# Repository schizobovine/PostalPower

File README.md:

# PostalPower
Postage-stamp (US) sized PCBs for stupid &amp; simple shit like DC-DC linear converters or LED drivers.

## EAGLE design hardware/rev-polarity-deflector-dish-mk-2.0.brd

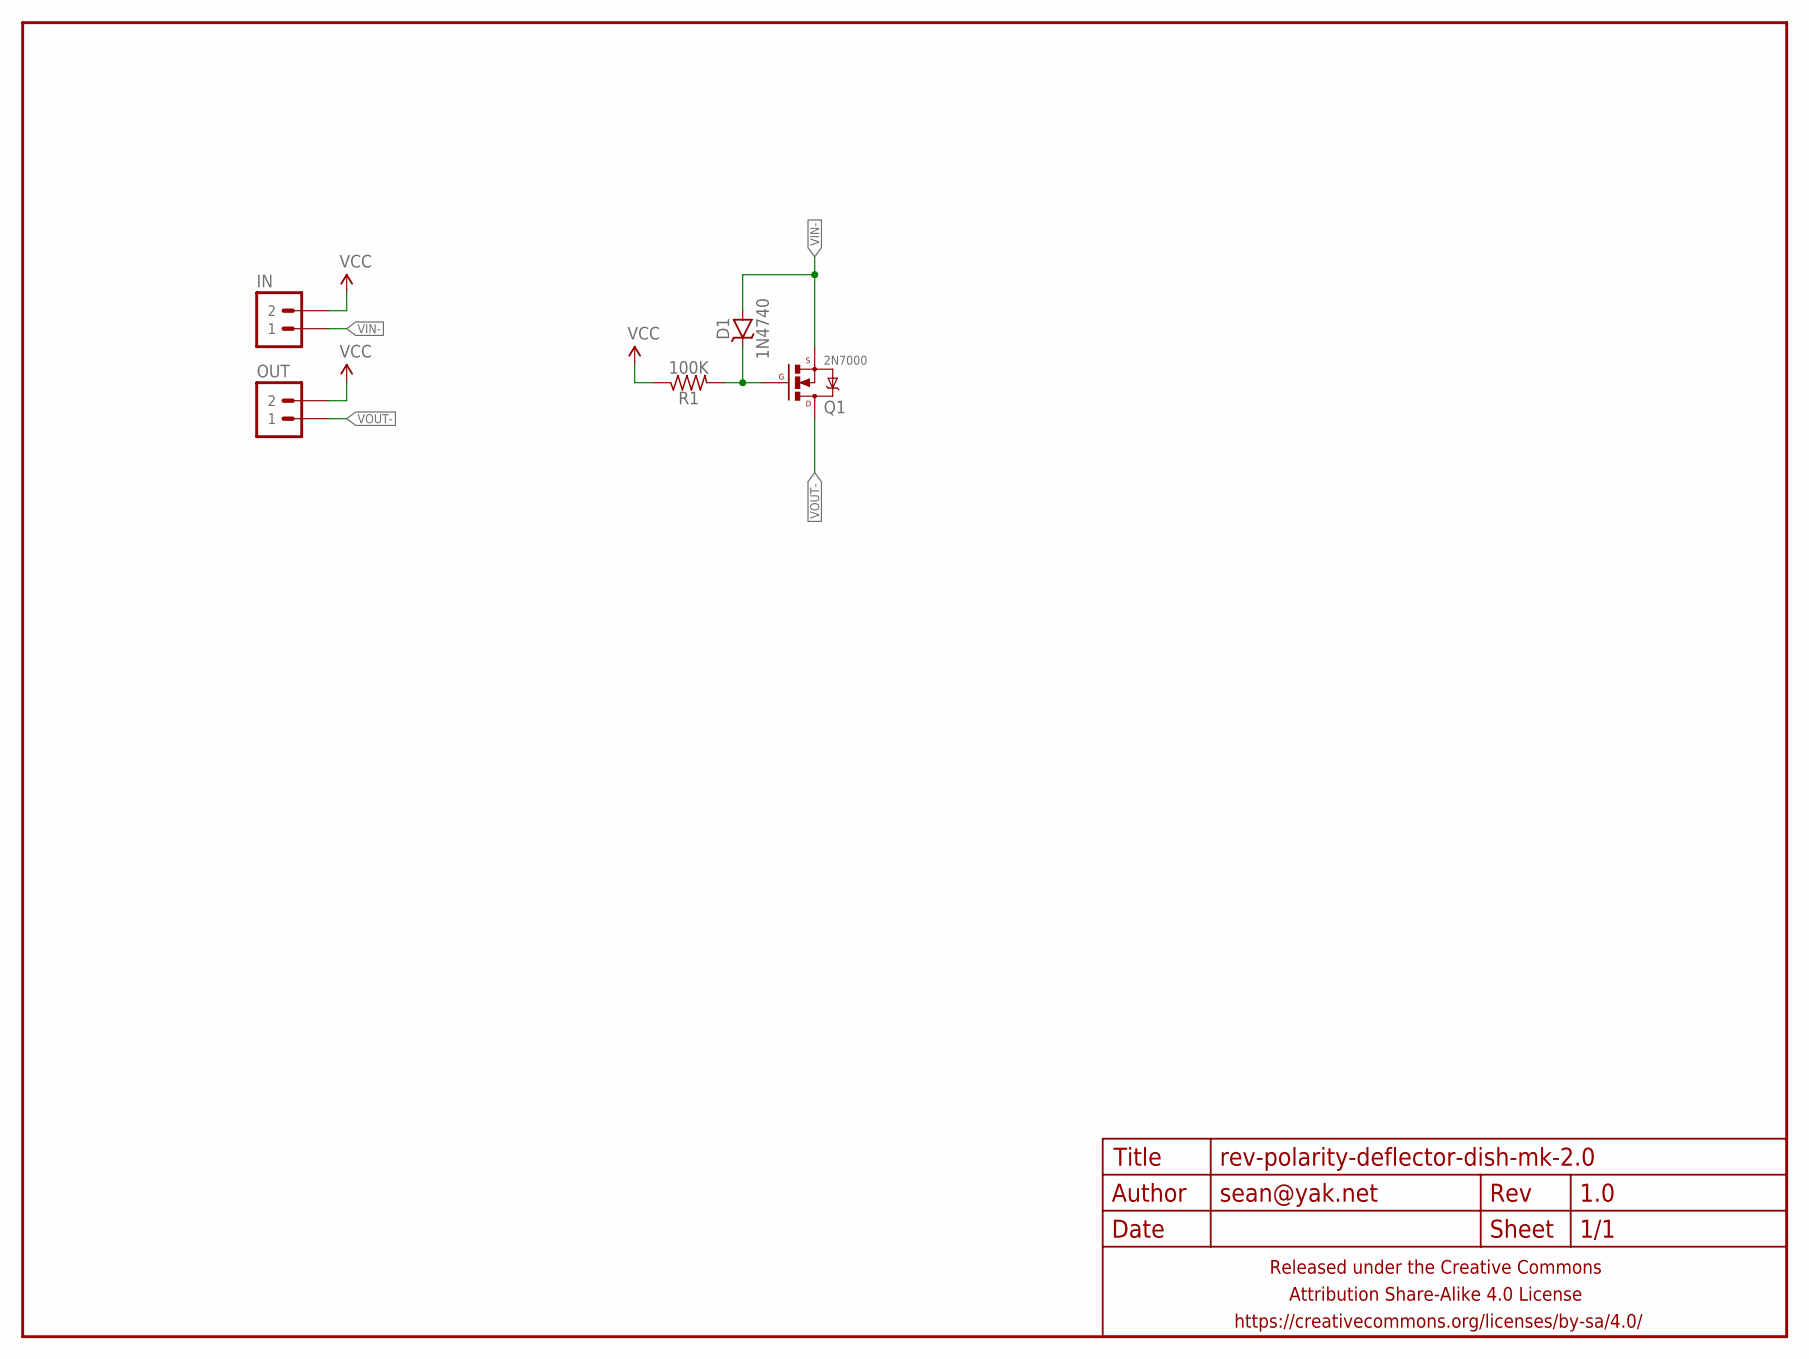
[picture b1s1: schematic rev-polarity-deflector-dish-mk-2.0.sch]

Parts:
D1: 1N4740; SOT23
FRAME1: FRAME-LETTERNO_PACKAGE; DUMMY
IN: M02PTH-CENTERED; 1X02-CENTER
OUT: M02PTH-CENTERED; 1X02-CENTER
Q1: 2N7000; SOT23
R1: 100K; R0603

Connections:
unnamed: D1.3 (C), Q1.1 (G), R1.2
VCC: IN.2, OUT.2, R1.1
VIN-: D1.1 (A), D1.2 (A), IN.1, Q1.2 (S)
VOUT-: OUT.1, Q1.3 (D)

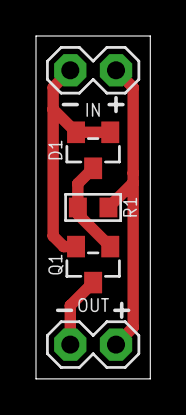
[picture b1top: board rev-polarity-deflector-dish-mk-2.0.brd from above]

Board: 2 copper layers, 6.3 x 19.1 mm, 6 parts (0 on the bottom side), 4 nets.

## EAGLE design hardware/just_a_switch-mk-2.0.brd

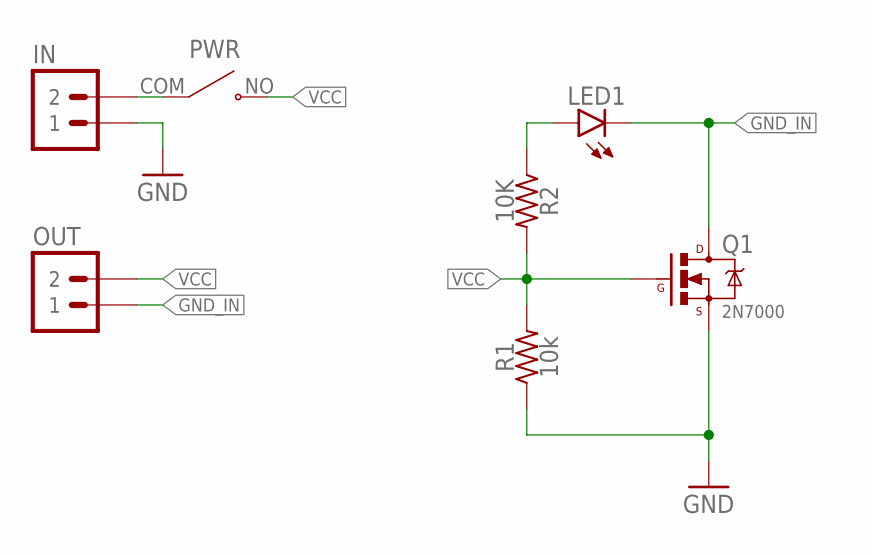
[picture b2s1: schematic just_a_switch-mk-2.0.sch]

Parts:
IN: M02PTH-CENTERED-R+; 1X02-CENTER-R+
LED1: LED3MM-LESS; LED3MM-LESSSILK
OUT: M02PTH-CENTERED-R+; 1X02-CENTER-R+
PWR: SWITCH-SPSTROCKER; SPST-ROCKER-3.81MM
Q1: 2N7000; TO-92-AMMO
R1: 10k; RESISTOR-AXIAL-PTH-5.08MM
R2: 10K; RESISTOR-AXIAL-PTH-5.08MM

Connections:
GND: IN.1, Q1.1 (S), R1.P$1 (1)
GND_IN: LED1.K (C), OUT.1, Q1.3 (D)
unnamed: IN.2, PWR.COM
unnamed: LED1.A, R2.P$1 (1)
VCC: OUT.2, PWR.NO, Q1.2 (G), R1.P$2 (2), R2.P$2 (2)

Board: 2 copper layers, 7 parts (2 on the bottom side), 5 nets, no tracks yet.

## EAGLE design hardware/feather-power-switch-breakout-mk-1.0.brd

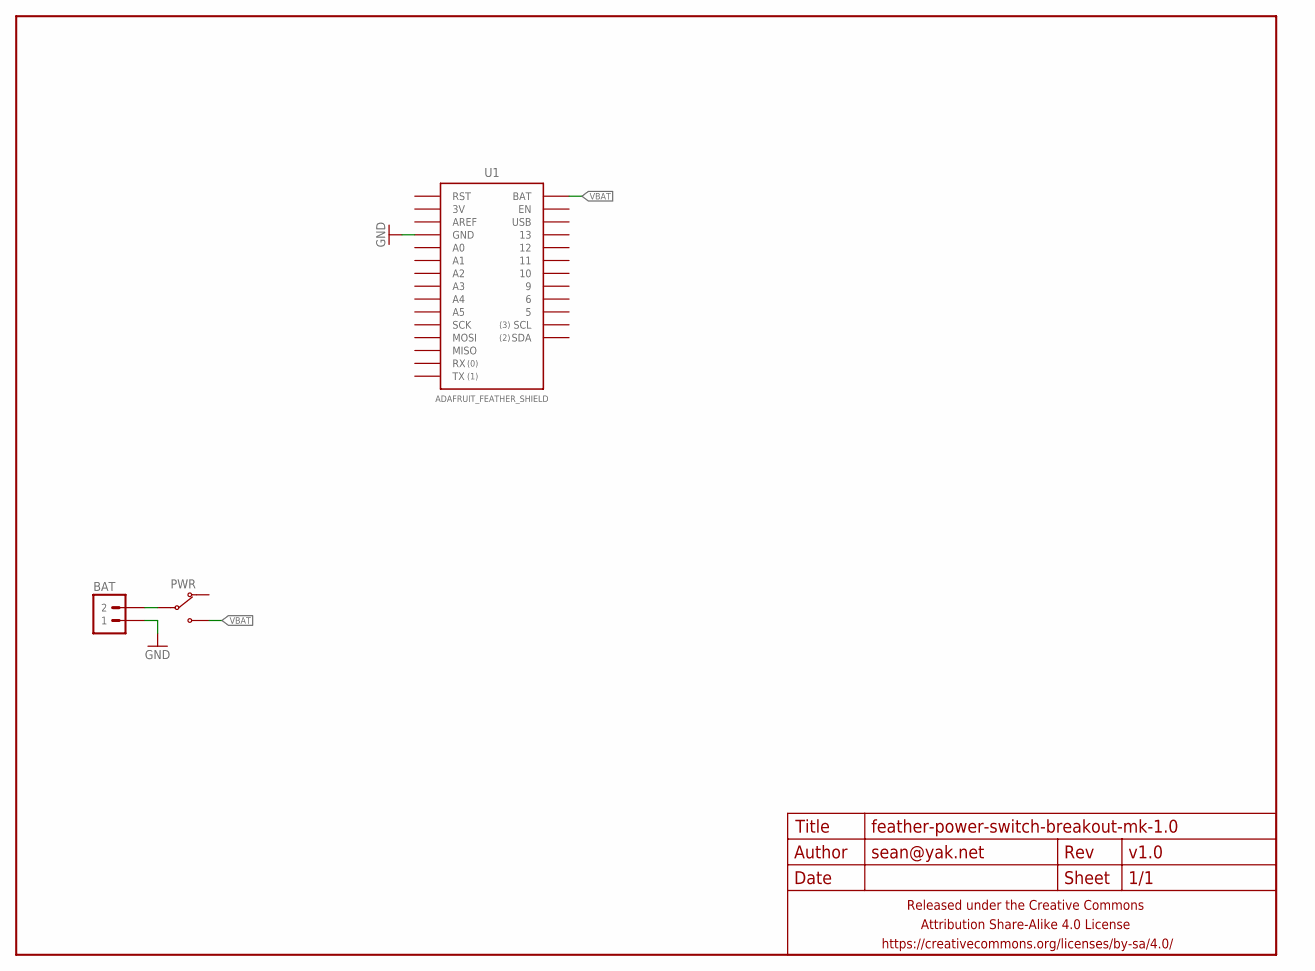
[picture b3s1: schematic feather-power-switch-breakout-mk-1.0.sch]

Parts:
BAT: M02JST-PTH-RA-R+; JST-2-PH-RA-PTH-R+
FRAME1: FRAME-LETTERNO_PACKAGE; DUMMY
PWR: SWITCH-SPDTPTH-RA-2.54MM; SPDT-RA-2.54MM
U1: ADAFRUIT_FEATHER_SHIELD; ADAFRUIT_FEATHER

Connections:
GND: BAT.1, U1.GND@0 (GND), U1.GND@1 (GND)
unnamed: BAT.2, PWR.2 (COM)
VBAT: PWR.3 (NO), U1.BAT

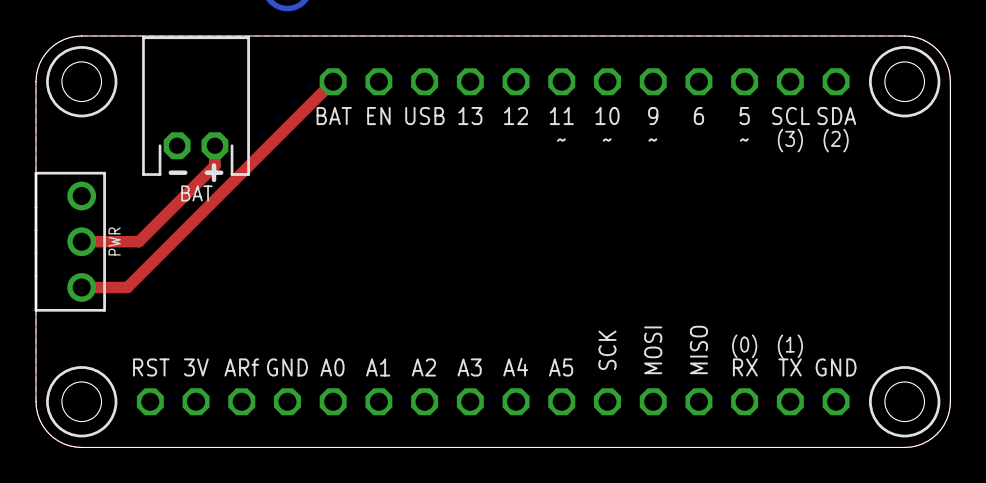
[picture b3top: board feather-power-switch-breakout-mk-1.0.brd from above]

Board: 2 copper layers, 50.8 x 22.9 mm, 5 parts (1 on the bottom side), 3 nets.

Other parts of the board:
U$1: COW_SMALL_METAL_NOTEXT

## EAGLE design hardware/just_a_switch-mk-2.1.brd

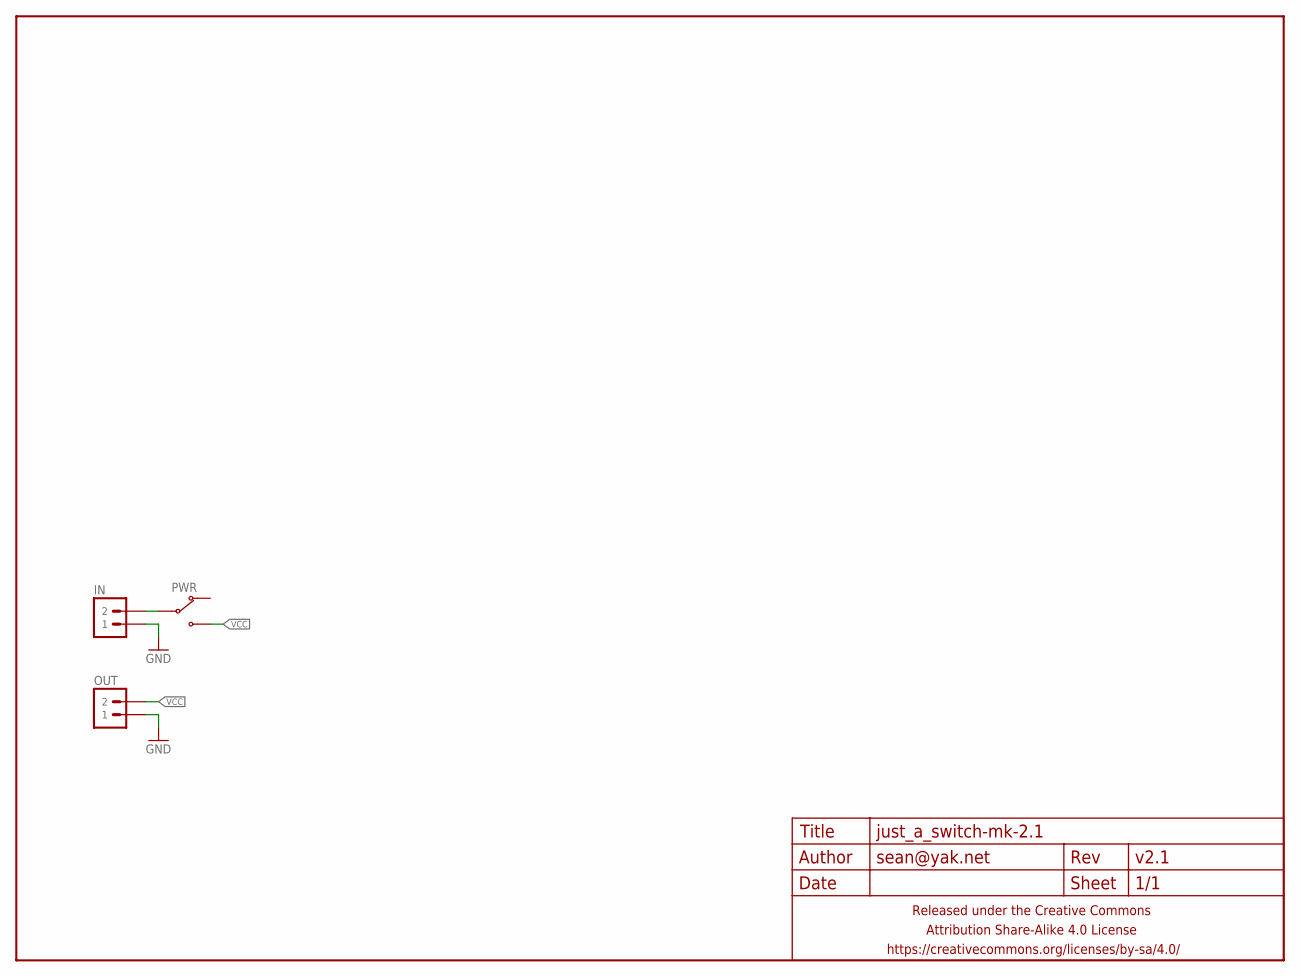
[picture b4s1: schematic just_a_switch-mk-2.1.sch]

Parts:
FRAME1: FRAME-LETTERNO_PACKAGE; DUMMY
IN: M02JST-PH-VERT-R+; JST-2-PH-VERT-PTH-R+
OUT: M02JST-PH-VERT-R+; JST-2-PH-VERT-PTH-R+
PWR: SWITCH-SPDTPTH-RA-2.54MM; SPDT-RA-2.54MM

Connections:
GND: IN.1, OUT.1
unnamed: IN.2, PWR.2 (COM)
VCC: OUT.2, PWR.3 (NO)

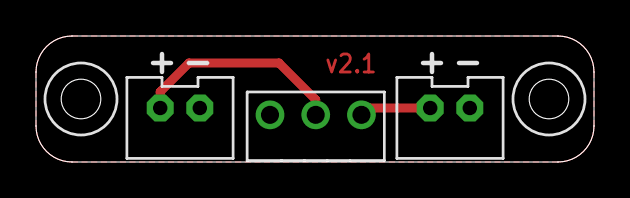
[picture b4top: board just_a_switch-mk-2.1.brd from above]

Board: 2 copper layers, 31.0 x 7.0 mm, 4 parts (0 on the bottom side), 3 nets.

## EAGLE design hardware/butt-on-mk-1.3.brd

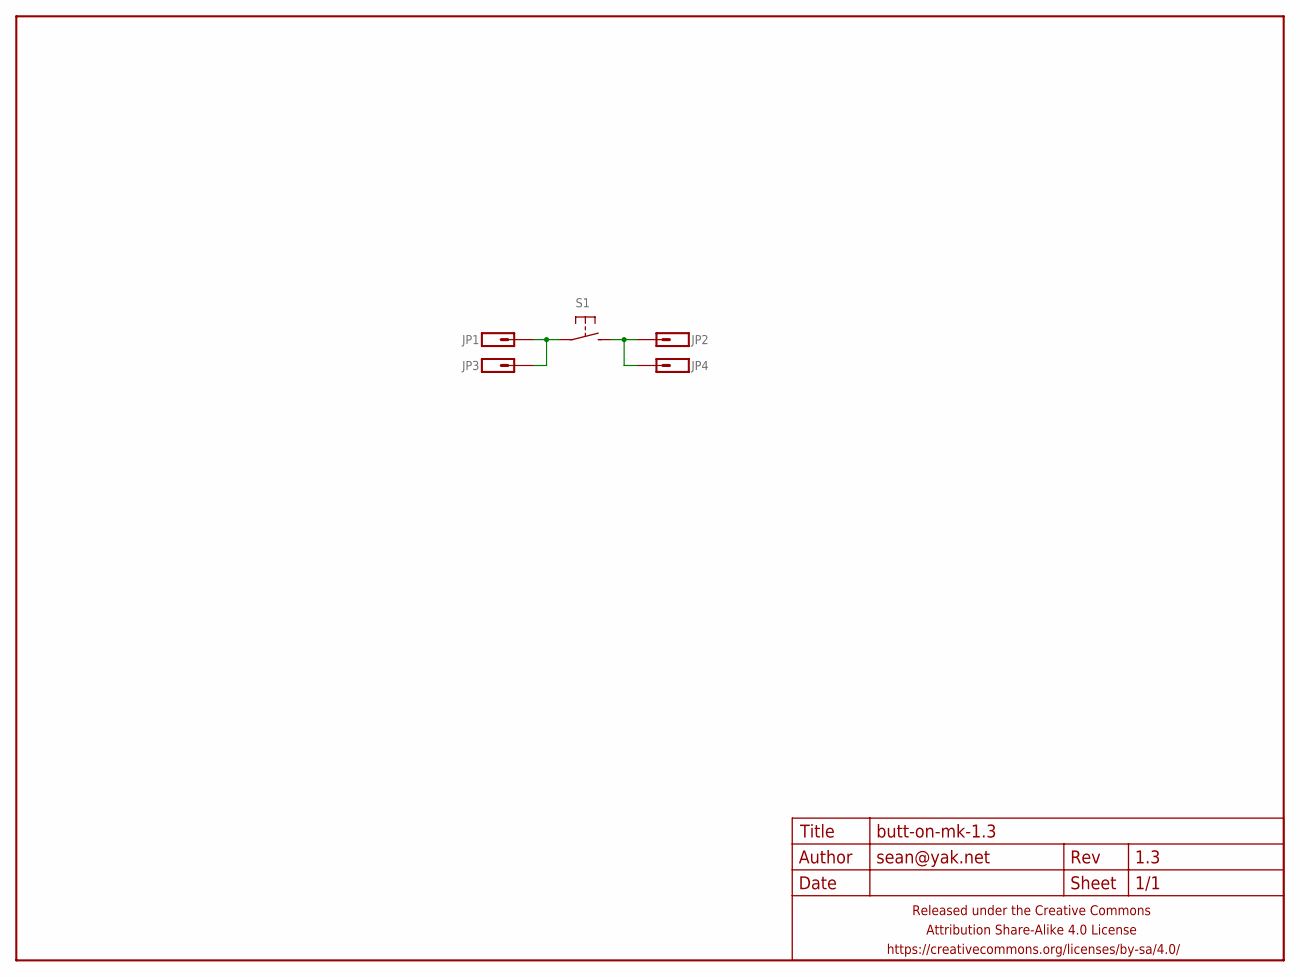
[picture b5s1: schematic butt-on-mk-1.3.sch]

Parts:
FRAME1: FRAME-LETTERNO_PACKAGE; DUMMY
JP1, JP2, JP3, JP4: M01PTH-0.9MM-NS; 1X01-0.9MM-NS
S1: SPST-NO-TACT6MM-PTH-SMALL-PADS; DTS-6-SMALL-PADS

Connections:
unnamed: JP1.1, JP3.1, S1.1, S1.2 (1)
unnamed: JP2.1, JP4.1, S1.3 (2), S1.4 (2)

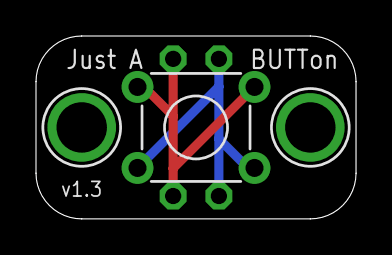
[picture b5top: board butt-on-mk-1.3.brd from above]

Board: 2 copper layers, 17.8 x 10.2 mm, 6 parts (0 on the bottom side), 2 nets.

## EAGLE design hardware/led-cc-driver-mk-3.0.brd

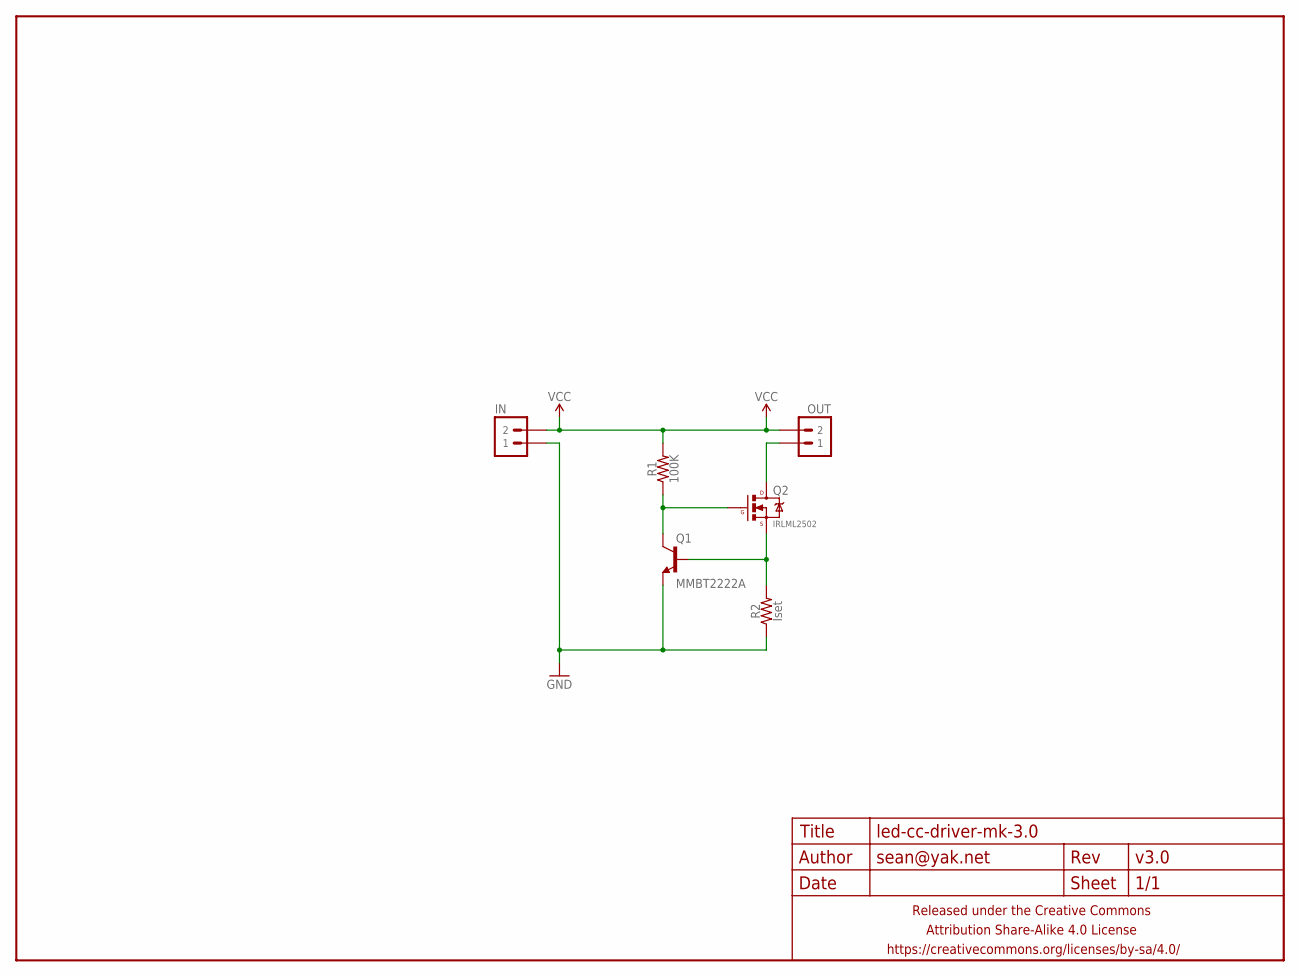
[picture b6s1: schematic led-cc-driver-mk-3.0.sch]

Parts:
FRAME1: FRAME-LETTERNO_PACKAGE; DUMMY
IN: M02PTH-CENTERED; 1X02-CENTER
OUT: M02PTH-CENTERED; 1X02-CENTER
Q1: MMBT2222A; SOT23
Q2: IRLML2502; SOT23
R1: 100K; R0603
R2: Iset; R0603

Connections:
GND: IN.1, Q1.2 (E), R2.1
unnamed: Q1.3 (C), Q2.1 (G), R1.1
unnamed: Q1.1 (B), Q2.2 (S), R2.2
unnamed: OUT.1, Q2.3 (D)
VCC: IN.2, OUT.2, R1.2

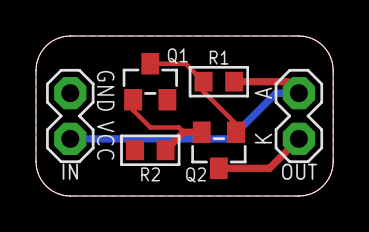
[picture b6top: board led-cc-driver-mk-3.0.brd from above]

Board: 2 copper layers, 16.5 x 8.9 mm, 8 parts (1 on the bottom side), 5 nets.

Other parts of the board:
U$1: COW_SMALL_NOTEXT

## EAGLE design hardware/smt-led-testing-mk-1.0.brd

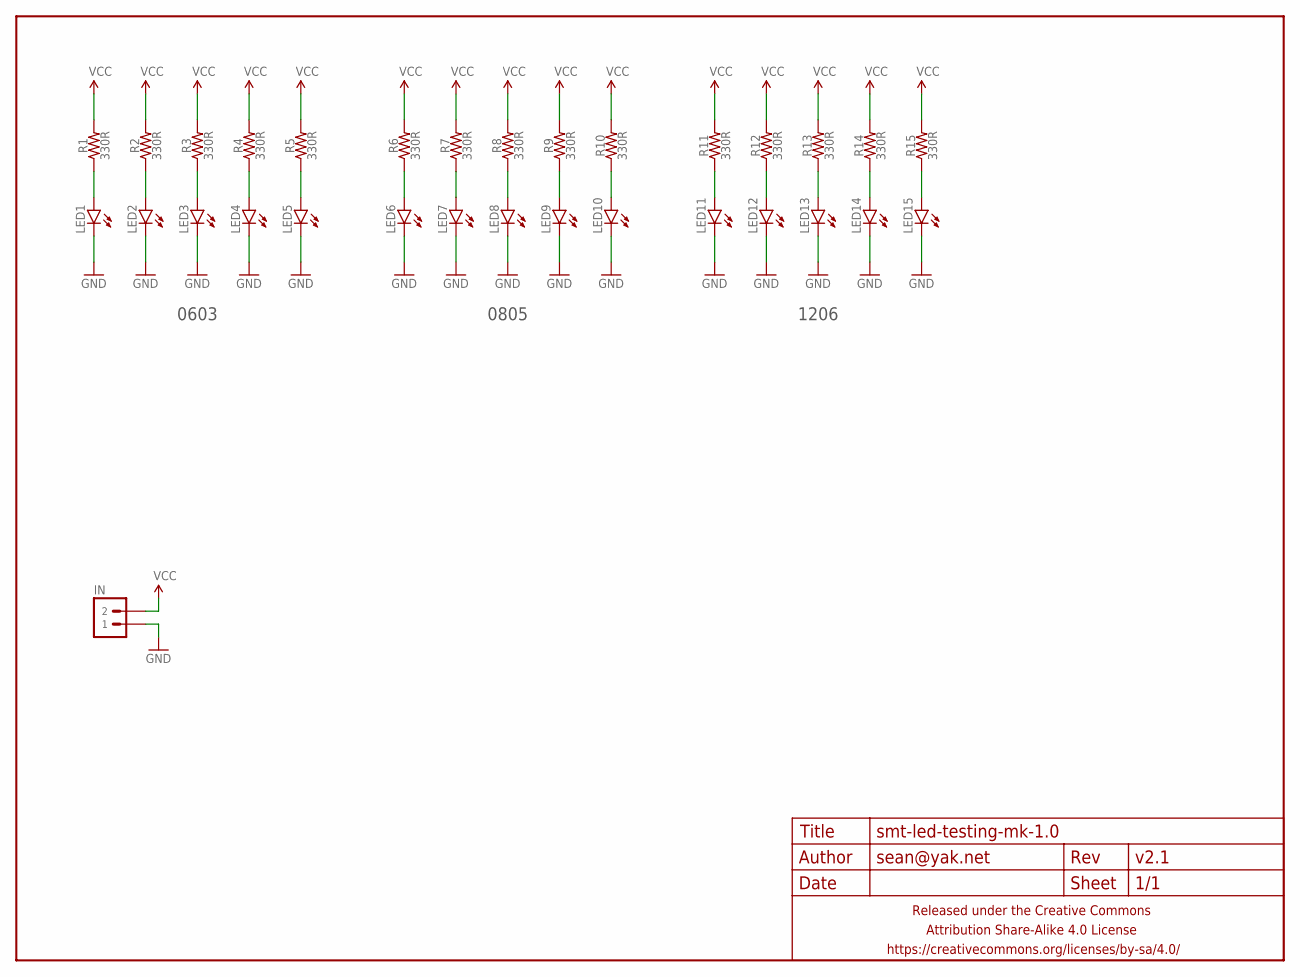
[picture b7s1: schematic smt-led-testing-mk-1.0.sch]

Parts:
FRAME1: FRAME-LETTERNO_PACKAGE; DUMMY
IN: M02PTH-CENTERED-R+; 1X02-CENTER-R+
LED1, LED2, LED3, LED4, LED5: LED0603; LED-0603
LED6, LED7, LED8, LED9, LED10: LED0805; LED-0805
LED11, LED12, LED13, LED14, LED15: LED1206; LED-1206
R1, R2, R3, R4, R5, R6, R7, R8, R9, R10, R11, R12, R13, R14, R15: 330R; R0603

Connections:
GND: IN.1, LED1.C, LED2.C, LED3.C, LED4.C, LED5.C, LED6.C, LED7.C, LED8.C, LED9.C, LED10.C, LED11.C, LED12.C, LED13.C, LED14.C, LED15.C
unnamed: LED1.A, R1.1
unnamed: LED2.A, R2.1
unnamed: LED3.A, R3.1
unnamed: LED4.A, R4.1
unnamed: LED5.A, R5.1
unnamed: LED6.A, R6.1
unnamed: LED7.A, R7.1
unnamed: LED8.A, R8.1
unnamed: LED9.A, R9.1
unnamed: LED10.A, R10.1
unnamed: LED11.A, R11.1
unnamed: LED12.A, R12.1
unnamed: LED13.A, R13.1
unnamed: LED14.A, R14.1
unnamed: LED15.A, R15.1
VCC: IN.2, R1.2, R2.2, R3.2, R4.2, R5.2, R6.2, R7.2, R8.2, R9.2, R10.2, R11.2, R12.2, R13.2, R14.2, R15.2

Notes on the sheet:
0603
0805
1206

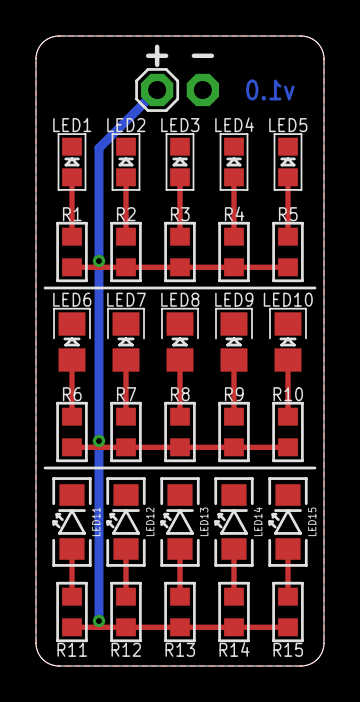
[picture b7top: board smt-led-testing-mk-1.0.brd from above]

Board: 2 copper layers, 16.0 x 35.0 mm, 32 parts (0 on the bottom side), 17 nets.

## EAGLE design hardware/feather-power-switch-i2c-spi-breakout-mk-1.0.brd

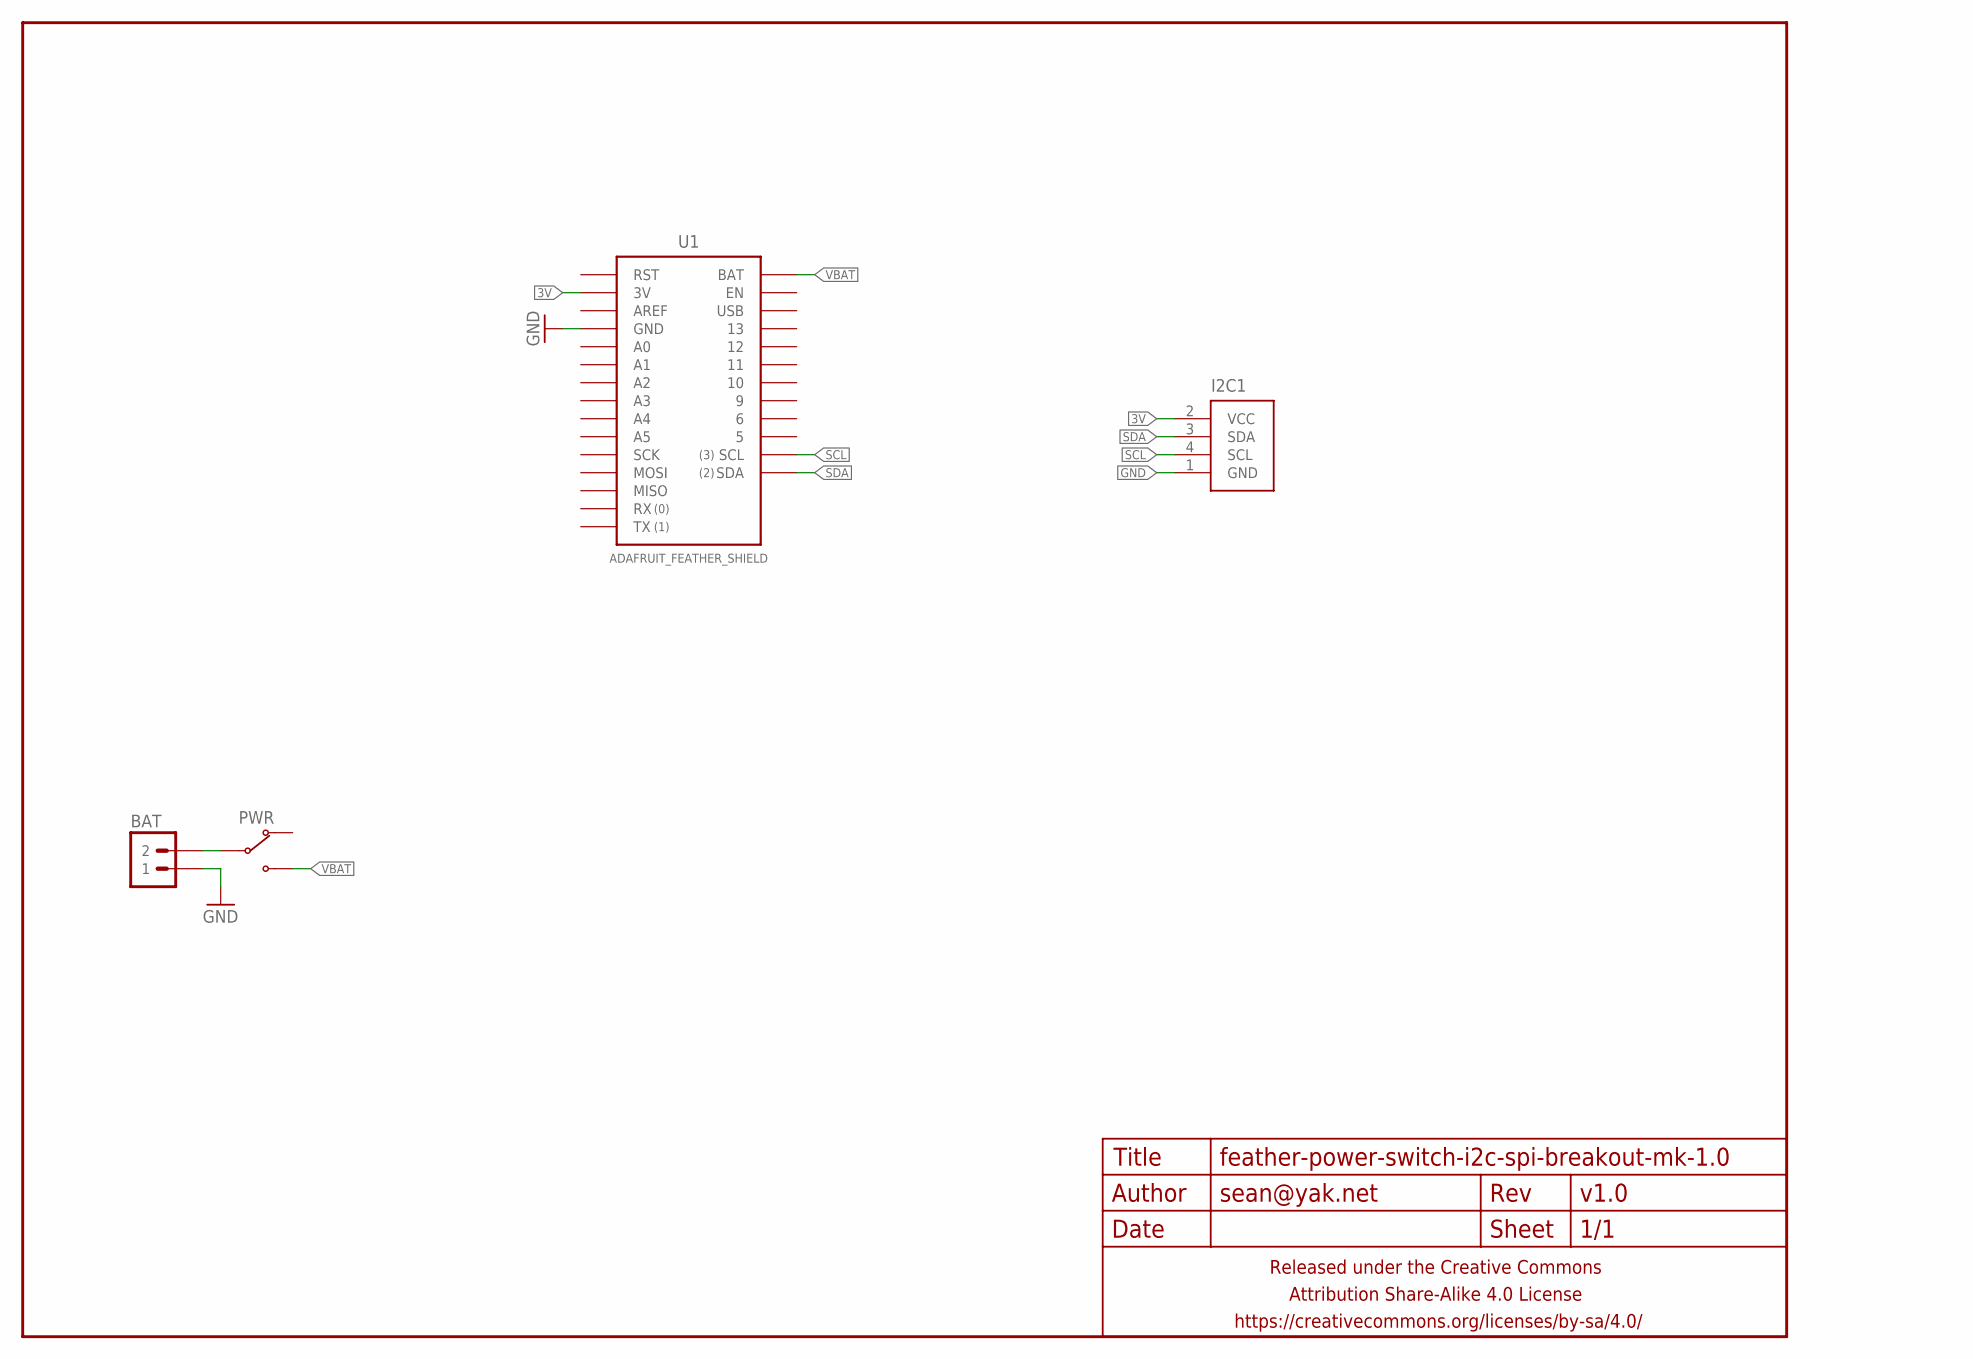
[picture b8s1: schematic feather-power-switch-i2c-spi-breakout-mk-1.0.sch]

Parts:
BAT: M02JST-PTH-RA-R+; JST-2-PH-RA-PTH-R+
FRAME1: FRAME-LETTERNO_PACKAGE; DUMMY
I2C1: M04-I2CJST-4-PH-VERT-CENTERED-I2C; JST-4-PH-VERT-PTH-CENTERED-I2C
PWR: SWITCH-SPDTPTH-RA-2.54MM; SPDT-RA-2.54MM
U1: ADAFRUIT_FEATHER_SHIELD; ADAFRUIT_FEATHER

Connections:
3V: I2C1.2 (VCC), U1.3V
GND: BAT.1, I2C1.1 (GND), U1.GND@0 (GND), U1.GND@1 (GND)
unnamed: BAT.2, PWR.2 (COM)
SCL: I2C1.4 (SCL), U1.SCL
SDA: I2C1.3 (SDA), U1.SDA
VBAT: PWR.3 (NO), U1.BAT

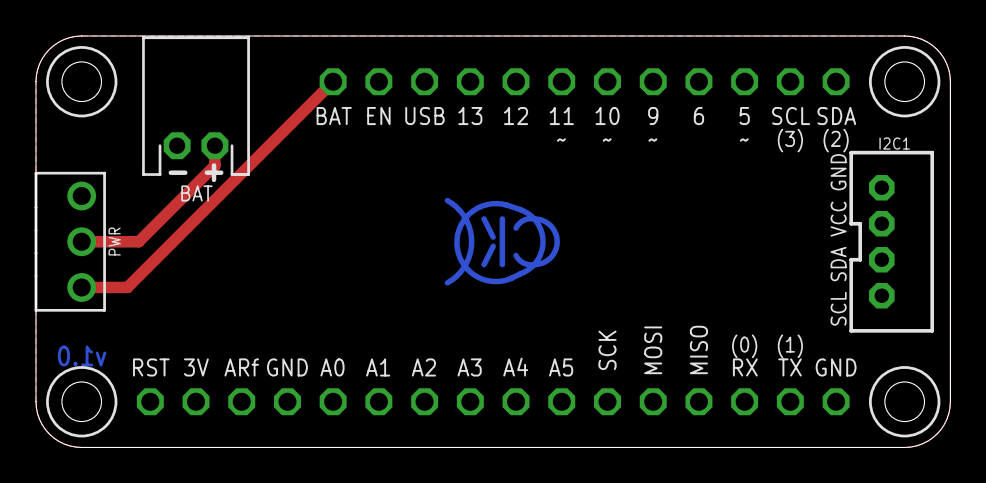
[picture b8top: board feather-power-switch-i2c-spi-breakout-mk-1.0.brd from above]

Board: 2 copper layers, 50.8 x 22.9 mm, 6 parts (1 on the bottom side), 6 nets.

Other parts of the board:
U$1: COW_SMALL_METAL_NOTEXT

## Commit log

2015-01-29 initial checkin of existing work
2015-01-29 copying these over to a better place
2015-01-29 these too
2015-04-09 constant current led driver based on common switching chip
2015-04-09 aslkdfjadsf
2015-04-09 new version with big-ass mosfet and a theoretical rgb version
2015-04-11 layout for cc driver and some dicking around with the rgb one
2015-04-11 new rgb board
2015-04-16 moved these and others to another project
2015-04-16 big brother to the previous version, using a power n-mosfet bent over to use the pcb as a heat sink
2015-04-16 renaming to match my current conventions
2015-04-17 new board includes zener and right angle JST PH connectors
2015-04-27 adding new designs: button breakout and level shifter. shush, i know these are basics.
2015-10-19 adding bunch of boards for rotary encoders
2015-10-19 tinier buttons
2015-10-19 level shifters minus a regulator
2015-10-22 marked up for fab
2015-10-22 more butts
2015-11-24 MOAR BOARDS
2017-01-12 some butt basic i2c level shifters for breadboard use/practice
2017-01-12 have some boards, dawg

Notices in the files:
parts and their libraries:
a_parts: Released under the Creative Commons Attribution Share-Alike 4.0 License
a_parts: https://creativecommons.org/licenses/by-sa/4.0
a_parts: Released under the Creative Commons
